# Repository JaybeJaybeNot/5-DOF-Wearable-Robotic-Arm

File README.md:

Robotic arms are a common project idea for engineers, providing the opportunity to tackle challenges such as feedback loops, PCB designing, firmware programming, and mechanical designing. The difficulty varies greatly, from using basic Microservos driven by Arduino to using industry-standard MCUs like the STM32 family to achieve impressive torque, precision, accuracy, and speed. 
Our design will lean somewhat to the right (industry-like) side of difficulty, utilizing the STM32F103C8Tx model of MCU's for performance, TMC motor drivers, the motors will be  2 NEMA 23 (QSH6018) for shoulders, and NEMA 17 (QSH6018) for elbow. Stepper motors are chosen for their high torque relative to their low costs, possibly getting away with $30 for each NEMA 23, depending on the seller. Gearboxes will be utilized for each motor to increase torque output. We'll also lean into the gritty, brutalist aesthetic of industry, partially because I had minimal CAD experience at the beginning of this project.
The "quirk" of our project is that the robotic arm will be wearable. Current design ideas include straps similar to those of a hiking backpack, but will possible change in the future due to ergonomic reasons or if I just came up with better ideas. To control the robotic arm, a GUI will be made with sliders that control each joint, and activators for motor modes (Stealthchop2, spreadcycle). 

This project was made out of a desire to learn embedded systems, firmware code, and basic mechanical design. It is also partially motivated by having Viktor from Arcane as my favorite character. 

|120R1                         |FerriteBead         |~                                                               |Inductor_SMD:L_0402_1005Metric                                                            |1  |FIELD6|
|------------------------------|--------------------|----------------------------------------------------------------|------------------------------------------------------------------------------------------|---|------|
|C1                            |680 uF              |~                                                               |Capacitor_SMD:C_1210_3225Metric                                                           |1  |      |
|C2                            |220 uF              |~                                                               |Capacitor_SMD:C_0603_1608Metric                                                           |1  |      |
|C3,C15                        |10 pF               |~                                                               |-- mixed values --                                                                        |2  |      |
|C4,C18,C19,C22,C25,C26,C27,C28|100nF               |~                                                               |-- mixed values --                                                                        |8  |      |
|C5,C24                        |2.2u, 6.3v          |~                                                               |-- mixed values --                                                                        |2  |      |
|C6,C7,C8,C9,C14               |100 nF              |~                                                               |Capacitor_SMD:C_0201_0603Metric                                                           |5  |      |
|C10                           |10 uF               |~                                                               |Capacitor_SMD:C_0201_0603Metric                                                           |1  |      |
|C11                           |10 nF               |~                                                               |Capacitor_SMD:C_0201_0603Metric                                                           |1  |      |
|C12,C13                       |1 uF                |~                                                               |Capacitor_SMD:C_0201_0603Metric                                                           |2  |      |
|C16,C17                       |22 uF               |~                                                               |Capacitor_SMD:C_0201_0603Metric                                                           |2  |      |
|C20,C29                       |100uF               |~                                                               |Capacitor_SMD:CP_Elec_5x3.9                                                               |2  |      |
|C21,C23                       |22nF                |~                                                               |Capacitor_SMD:C_0201_0603Metric                                                           |2  |      |
|D1                            |1N5824              |http://www.vishay.com/docs/88526/1n5820.pdf                     |Diode_THT:D_DO-201AD_P3.81mm_Vertical_AnodeUp                                             |1  |      |
|D2                            |LED                 |~                                                               |LED_THT:LED_D2.0mm_W4.0mm_H2.8mm_FlatTop                                                  |1  |      |
|J1,J2                         |Conn_01x04_Pin      |~                                                               |Connector:FanPinHeader_1x04_P2.54mm_Vertical                                              |2  |      |
|J3,J4,J5,J6,J7,J8,J9,J10      |Screw_Terminal_01x01|~                                                               |TerminalBlock_MetzConnect:TerminalBlock_MetzConnect_360271_1x01_Horizontal_ScrewM3.0_Boxed|8  |      |
|J11                           |Supply anode        |~                                                               |TerminalBlock_Phoenix:TerminalBlock_Phoenix_MKDS-1,5-2-5.08_1x02_P5.08mm_Horizontal       |1  |      |
|J12                           |Supply Cathode      |~                                                               |TerminalBlock_Phoenix:TerminalBlock_Phoenix_MKDS-1,5-2-5.08_1x02_P5.08mm_Horizontal       |1  |      |
|L1                            |33 uH               |~                                                               |Inductor_SMD:L_0603_1608Metric                                                            |1  |      |
|P1                            |USB_C_Plug_USB2.0   |https://www.usb.org/sites/default/files/documents/usb_type-c.zip|Connector_USB:USB_C_Plug_JAE_DX07P024AJ1                                                  |1  |      |
|R1                            |10k                 |~                                                               |Resistor_SMD:R_0603_1608Metric                                                            |1  |      |
|R2,R11,R12                    |5.1kR               |~                                                               |Resistor_SMD:R_0603_1608Metric                                                            |3  |      |
|R3,R4,R5,R6                   |1.5k                |~                                                               |Resistor_SMD:R_0603_1608Metric                                                            |4  |      |
|R7,R8,R9,R10                  |0.05 R              |~                                                               |Resistor_SMD:R_0603_1608Metric                                                            |4  |      |
|RREF1,RREF2                   |0.05R               |~                                                               |Resistor_SMD:R_0603_1608Metric                                                            |2  |      |
|SW1                           |SW_DPST_x2          |~                                                               |Button_Switch_SMD:SW_SPST_REED_CT05-XXXX-J1                                               |1  |      |
|SW2                           |SW_SPDT             |~                                                               |Button_Switch_THT:SW_Slide_SPDT_Straight_CK_OS102011MS2Q                                  |1  |      |
|U1                            |STM32F103C8Tx       |https://www.st.com/resource/en/datasheet/stm32f103c8.pdf        |Package_QFP:LQFP-48_7x7mm_P0.5mm                                                          |1  |      |
|U2                            |AMS1117-3.3         |http://www.advanced-monolithic.com/pdf/ds1117.pdf               |Package_TO_SOT_SMD:SOT-223-3_TabPin2                                                      |1  |      |
|U3,U5                         |TMC2209-LA          |TMC2209-LA                                                      |footprints:QFN28_5X5_TRI                                                                  |2  |      |
|U4                            |LM2596S-3.3         |http://www.ti.com/lit/ds/symlink/lm2596.pdf                     |Package_TO_SOT_SMD:TO-263-5_TabPin3                                                       |1  |      |
|Y1                            |16 MHz              |~                                                               |Crystal:Crystal_SMD_0603-4Pin_6.0x3.5mm                                                   |1  |      |

|Part Name                     |FIXED Modular design|FIELD3                                                          |FIELD4                                                                                    |FIELD5|FIELD6                   |FIELD7     |FIELD8   |FIELD9  |FIELD10|FIELD11 |FIELD12      |FIELD13     |
|------------------------------|--------------------|----------------------------------------------------------------|------------------------------------------------------------------------------------------|------|-------------------------|-----------|---------|--------|-------|--------|-------------|------------|
|Working BOM                   |as of July 31, 2025 at 12:54:05 AM UTC|                                                                |                                                                                          |      |                         |           |         |        |       |        |             |            |
|Exported by                   |yaoy26@okemosk12.net|                                                                |                                                                                          |      |                         |           |         |        |       |        |             |            |
|Time of Export                |12:54 AM Jul 31, 2025|                                                                |                                                                                          |      |                         |           |         |        |       |        |             |            |
|                              |                    |                                                                |                                                                                          |      |                         |           |         |        |       |        |             |            |
|Level                         |Part Number         |Part Name                                                       |External Component                                                                        |Milestone|Description              |Link       |Lifecycle|Revision|State  |Quantity|Material Name|Change Order|
|1                             |FIXED Modular design|FIXED Modular design                                            |                                                                                          |      |                         |           |         |        |Working|1       |Steel        |            |
|1.1                           |90304A311_Steel Pan Head Torx Screws|90304A311_Steel Pan Head Torx Screws                            |External                                                                                  |      |STEP AP203               |           |         |        |Working|1       |Steel        |            |
|1.2                           |FLANGE_COUPLING_W_GRUB_SCREW_ASM|flange_coupling_w_grub_screw_asm                                |External                                                                                  |      |                         |[(May not work on some browsers)](https://www.aliexpress.us/item/3256801265414698.html?gatewayAdapt=glo2usa4itemAdapt)|         |        |Working|1       |Steel        |            |
|1.2.1                         |M6X8_GRUB_SCREW     |M6X8_GRUB_SCREW                                                 |                                                                                          |      |NOT SPECIFIED            |           |         |        |Working|1       |Steel        |            |
|1.2.2                         |FLANGE_COUPLING_W_KEYWAY|FLANGE_COUPLING_W_KEYWAY                                        |                                                                                          |      |NOT SPECIFIED            |https://www.aliexpress.us/item/2255800648228548.html?spm=a2g0o.cart.0.0.35c13c00J1egBJ&mp=1&gatewayAdapt=glo2usa4itemAdapt|         |        |Working|3       |Steel        |            |
|1.3                           |23HS22-2804S-HG50   |23HS22-2804S-HG50                                               |External                                                                                  |      |STEP AP214               |https://www.omc-stepperonline.com/nema-23-stepper-motor-l-56mm-gear-ratio-50-1-high-precision-planetary-gearbox-23hs22-2804s-hg50?srsltid=AfmBOorzKo3zYEa1jqBecvxOFDW23BkeehO4uh2gfFv6ItN-vEymc9Z2|         |        |Working|4       |Steel        |            |
|1.4.1                         |M6X8_GRUB_SCREW     |M6X8_GRUB_SCREW (2)                                             |                                                                                          |      |NOT SPECIFIED            |           |         |        |Working|1       |Steel        |            |
|                              |                    |                                                                |                                                                                          |      |                         |           |         |        |       |        |             |            |
|1.5                           |90304A311_Steel Pan Head Torx Screws|90304A311_Steel Pan Head Torx Screws v1 (1)                     |                                                                                          |      |STEP AP203               |           |         |        |Working|1       |Steel        |            |
|1.6                           |Base2               |Base2                                                           |                                                                                          |      |                         |           |         |        |Working|1       |Steel        |            |
|1.7                           |Link 2              |Link 2                                                          |                                                                                          |      |                         |           |         |        |Working|1       |Steel        |            |
|1.7.1                         |ST-M2               |ST-M2 v1 (1)                                                    |                                                                                          |      |STEP AP214               |https://www.omc-stepperonline.com/nema-23-bracket-for-stepper-motor-and-geared-stepper-motor-alloy-steel-bracket-st-m2?language=en&currency=USD&srsltid=AfmBOooK8qa6g0IWq9fvevblhgD680OPMLwRSRrIZ5VgKmFI16Q3KWzENZg&gQT=1|         |        |Working|4       |Steel        |            |
|1.9                           |Base1               |Base1                                                           |                                                                                          |      |                         |           |         |        |Working|1       |Steel        |            |

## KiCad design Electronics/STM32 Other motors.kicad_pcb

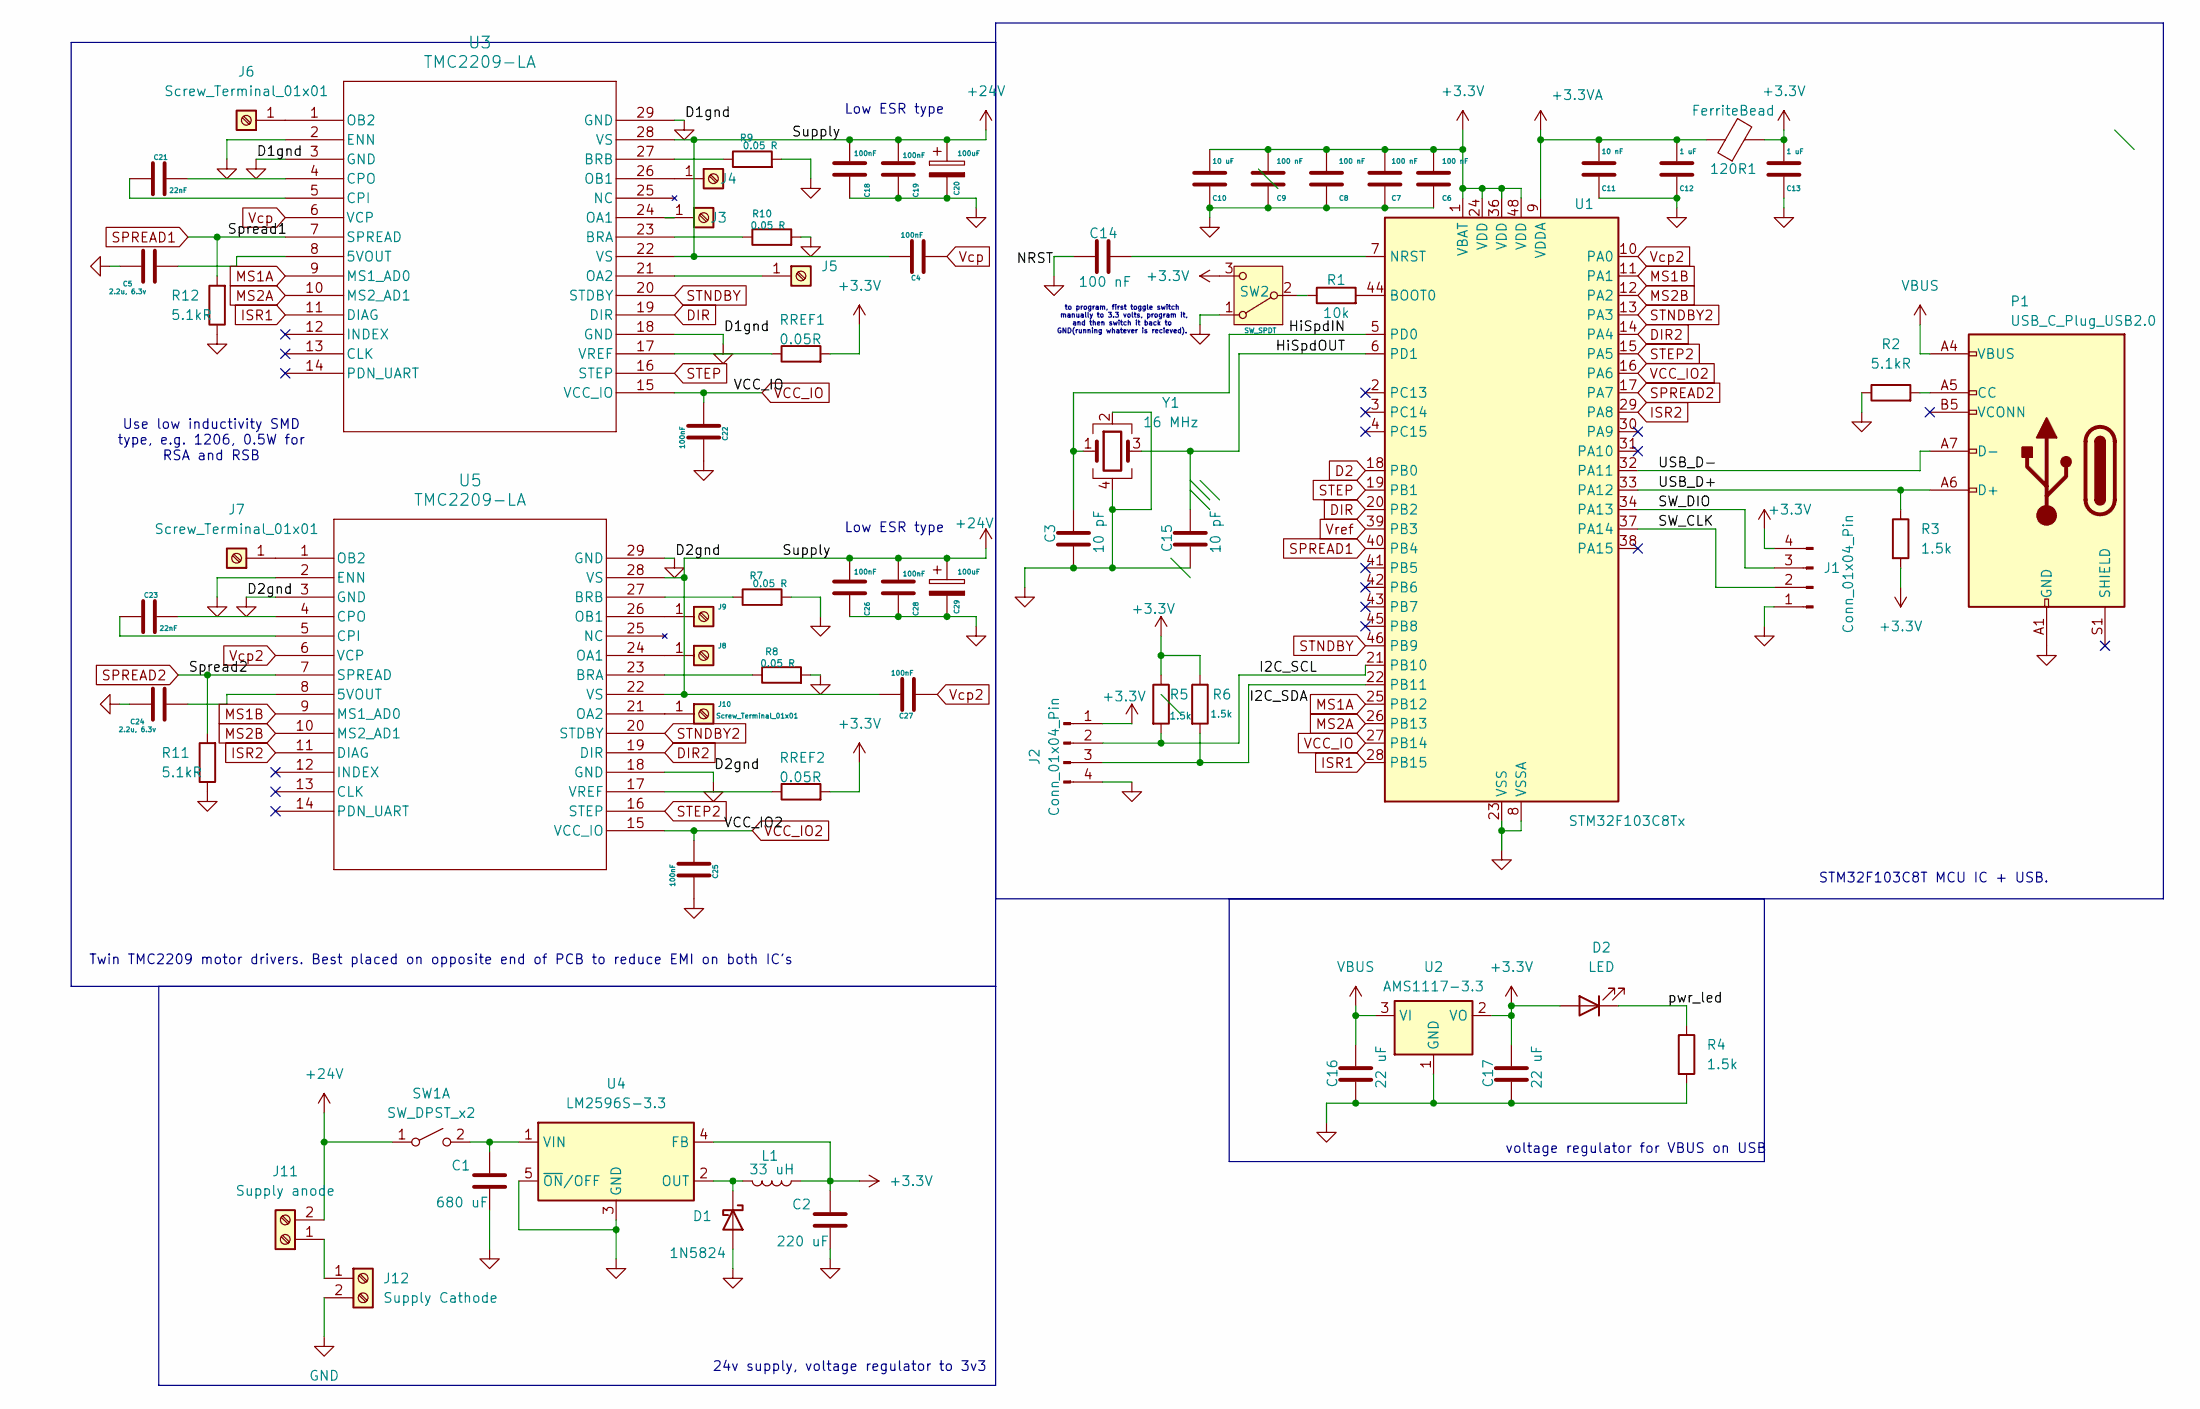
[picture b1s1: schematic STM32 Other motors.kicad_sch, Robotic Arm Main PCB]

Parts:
120R1: FerriteBead; L_0402_1005Metric
C1: 680 uF; C_1210_3225Metric
C2: 220 uF; C_0603_1608Metric
C3: 10 pF; C_0402_1005Metric
C4: 100nF; C_0402_1005Metric
C5: 2.2u, 6.3v; C_0402_1005Metric
C6, C7, C8, C9, C14: 100 nF; C_0201_0603Metric
C10: 10 uF; C_0201_0603Metric
C11: 10 nF; C_0201_0603Metric
C12, C13: 1 uF; C_0201_0603Metric
C15: 10 pF; C_0201_0603Metric
C16, C17: 22 uF; C_0201_0603Metric
C18, C19, C22, C25, C26, C27, C28: 100nF; C_0201_0603Metric
C20, C29: 100uF; CP_Elec_5x3.9
C21, C23: 22nF; C_0201_0603Metric
C24: 2.2u, 6.3v; C_0201_0603Metric
D1: 1N5824; D_DO-201AD_P3.81mm_Vertical_AnodeUp
D2: LED; LED_D2.0mm_W4.0mm_H2.8mm_FlatTop
J1, J2: Conn_01x04_Pin; FanPinHeader_1x04_P2.54mm_Vertical
J3, J4, J5, J6, J7, J8, J9, J10: Screw_Terminal_01x01; TerminalBlock_MetzConnect_360271_1x01_Horizontal_ScrewM3.0_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
J11: Supply anode; TerminalBlock_Phoenix_MKDS-1,5-2-5.08_1x02_P5.08mm_Horizont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
J12: Supply Cathode; TerminalBlock_Phoenix_MKDS-1,5-2-5.08_1x02_P5.08mm_Horizont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
L1: 33 uH; L_0603_1608Metric
P1: USB_C_Plug_USB2.0; USB_C_Plug_JAE_DX07P024AJ1
R1: 10k; R_0603_1608Metric
R2, R11, R12: 5.1kR; R_0603_1608Metric
R3, R4, R5, R6: 1.5k; R_0603_1608Metric
R7, R8, R9, R10: 0.05 R; R_0603_1608Metric
RREF1, RREF2: 0.05R; R_0603_1608Metric
SW1: SW_DPST_x2; SW_SPST_REED_CT05-XXXX-J1
SW2: SW_SPDT; SW_Slide_SPDT_Straight_CK_OS102011MS2Q
U1: STM32F103C8Tx; LQFP-48_7x7mm_P0.5mm
U2: AMS1117-3.3; SOT-223-3_TabPin2
U3, U5: TMC2209-LA; QFN28_5X5_TRI
U4: LM2596S-3.3; TO-263-5_TabPin3
Y1: 16 MHz; Crystal_SMD_0603-4Pin_6.0x3.5mm

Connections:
+3.3V: 120R1.2, C2.2, C6.2, C7.2, C8.2, C9.2, C10.2, C13.2, C17.1, D2.2 (A), J1.4, J2.1, L1.1, R3.2, R5.1, R6.1, RREF1.2, RREF2.2, SW2.3 (C), U1.1 (VBAT), U1.24 (VDD), U1.36 (VDD), U1.48 (VDD), U2.2 (VO), U4.4 (FB)
+3.3VA: 120R1.1, C11.2, C12.2, U1.9 (VDDA)
+24V: C4.2, C18.2, C19.2, C20.1, C26.2, C27.2, C28.2, C29.1, J11.2, SW1.1 (A), U3.22 (VS), U3.28 (VS), U5.22 (VS), U5.28 (VS)
/HiSpdIN: C3.1, U1.5 (PD0), Y1.1
/HiSpdOUT: C15.1, U1.6 (PD1), Y1.3
/I2C_SCL: J2.2, R5.2, U1.21 (PB10)
/I2C_SDA: J2.3, R6.2, U1.22 (PB11)
/SW_CLK: J1.2, U1.37 (PA14)
/SW_DIO: J1.3, U1.34 (PA13)
/USB_D+: P1.A6 (D+), R3.1, U1.33 (PA12)
/USB_D-: P1.A7 (D-), U1.32 (PA11)
/pwr_led: D2.1 (K), R4.1
D2: U1.18 (PB0)
DIR: U1.20 (PB2), U3.19 (DIR)
DIR2: U1.14 (PA4), U5.19 (DIR)
GND: C1.1, C2.1, C3.2, C5.1, C6.1, C7.1, C8.1, C9.1, C10.1, C11.1, C12.1, C13.1, C14.2, C15.2, C16.2, C17.2, C18.1, C19.1, C20.2, C22.2, C24.1, C25.2, C26.1, C28.1, C29.2, D1.2 (A), J1.1, J2.4, J12.2, P1.A1 (GND), P1.A12 (GND), P1.B1 (GND), P1.B12 (GND), R2.1, R4.2, R7.2, R8.2, R9.2, R10.2, R11.1, R12.1, SW2.1 (A), U1.8 (VSSA), U1.23 (VSS), U1.35 (VSS), U1.47 (VSS), U2.1 (GND), U3.2 (ENN), U3.3 (GND), U3.18 (GND), U3.29 (GND), U4.3 (GND), U4.5 (~ON/OFF), U5.2 (ENN), U5.3 (GND), U5.18 (GND), U5.29 (GND), Y1.2, Y1.4
ISR1: U1.28 (PB15), U3.11 (DIAG)
ISR2: U1.29 (PA8), U5.11 (DIAG)
MS1A: U1.25 (PB12), U3.9 (MS1_AD0)
MS1B: U1.11 (PA1), U5.9 (MS1_AD0)
MS2A: U1.26 (PB13), U3.10 (MS2_AD1)
MS2B: U1.12 (PA2), U5.10 (MS2_AD1)
unnamed: D1.1 (K), L1.2, U4.2 (OUT)
unnamed: J3.1, U3.24 (OA1)
unnamed: J4.1, U3.26 (OB1)
unnamed: J5.1, U3.21 (OA2)
unnamed: J6.1, U3.1 (OB2)
unnamed: J7.1, U5.1 (OB2)
unnamed: J8.1, U5.24 (OA1)
unnamed: J9.1, U5.26 (OB1)
unnamed: J10.1, U5.21 (OA2)
unnamed: J11.1, J12.1
unnamed: P1.A5 (CC), R2.2
unnamed: C1.2, SW1.2 (B), U4.1 (VIN)
unnamed: R1.1, SW2.2 (B)
unnamed: R1.2, U1.44 (BOOT0)
unnamed: C14.1, U1.7 (NRST)
unnamed: C5.2, U3.8 (5VOUT)
unnamed: R10.1, U3.23 (BRA)
unnamed: R9.1, U3.27 (BRB)
unnamed: C21.1, U3.5 (CPI)
unnamed: C21.2, U3.4 (CPO)
unnamed: RREF1.1, U3.17 (VREF)
unnamed: C24.2, U5.8 (5VOUT)
unnamed: R8.1, U5.23 (BRA)
unnamed: R7.1, U5.27 (BRB)
unnamed: C23.1, U5.5 (CPI)
unnamed: C23.2, U5.4 (CPO)
unnamed: RREF2.1, U5.17 (VREF)
SPREAD1: R12.2, U1.40 (PB4), U3.7 (SPREAD)
SPREAD2: R11.2, U1.17 (PA7), U5.7 (SPREAD)
STEP: U1.19 (PB1), U3.16 (STEP)
STEP2: U1.15 (PA5), U5.16 (STEP)
STNDBY: U1.46 (PB9), U3.20 (STDBY)
STNDBY2: U1.13 (PA3), U5.20 (STDBY)
VBUS: C16.1, P1.A4 (VBUS), P1.A9 (VBUS), P1.B4 (VBUS), P1.B9 (VBUS), U2.3 (VI)
VCC_IO: C22.1, U1.27 (PB14), U3.15 (VCC_IO)
VCC_IO2: C25.1, U1.16 (PA6), U5.15 (VCC_IO)
Vcp: C4.1, U3.6 (VCP)
Vcp2: C27.1, U1.10 (PA0), U5.6 (VCP)
Vref: U1.39 (PB3)

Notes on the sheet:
Twin TMC2209 motor drivers. Best placed on opposite end of PCB to reduce EMI on both IC's
24v supply, voltage regulator to 3v3
to program, first toggle switch manually to 3.3 volts, program it, and then switch it back to GND(running whatever is recieved).
Low ESR type
STM32F103C8T MCU IC + USB.
Use low inductivity SMD type, e.g. 1206, 0.5W for RSA and RSB
voltage regulator for VBUS on USB

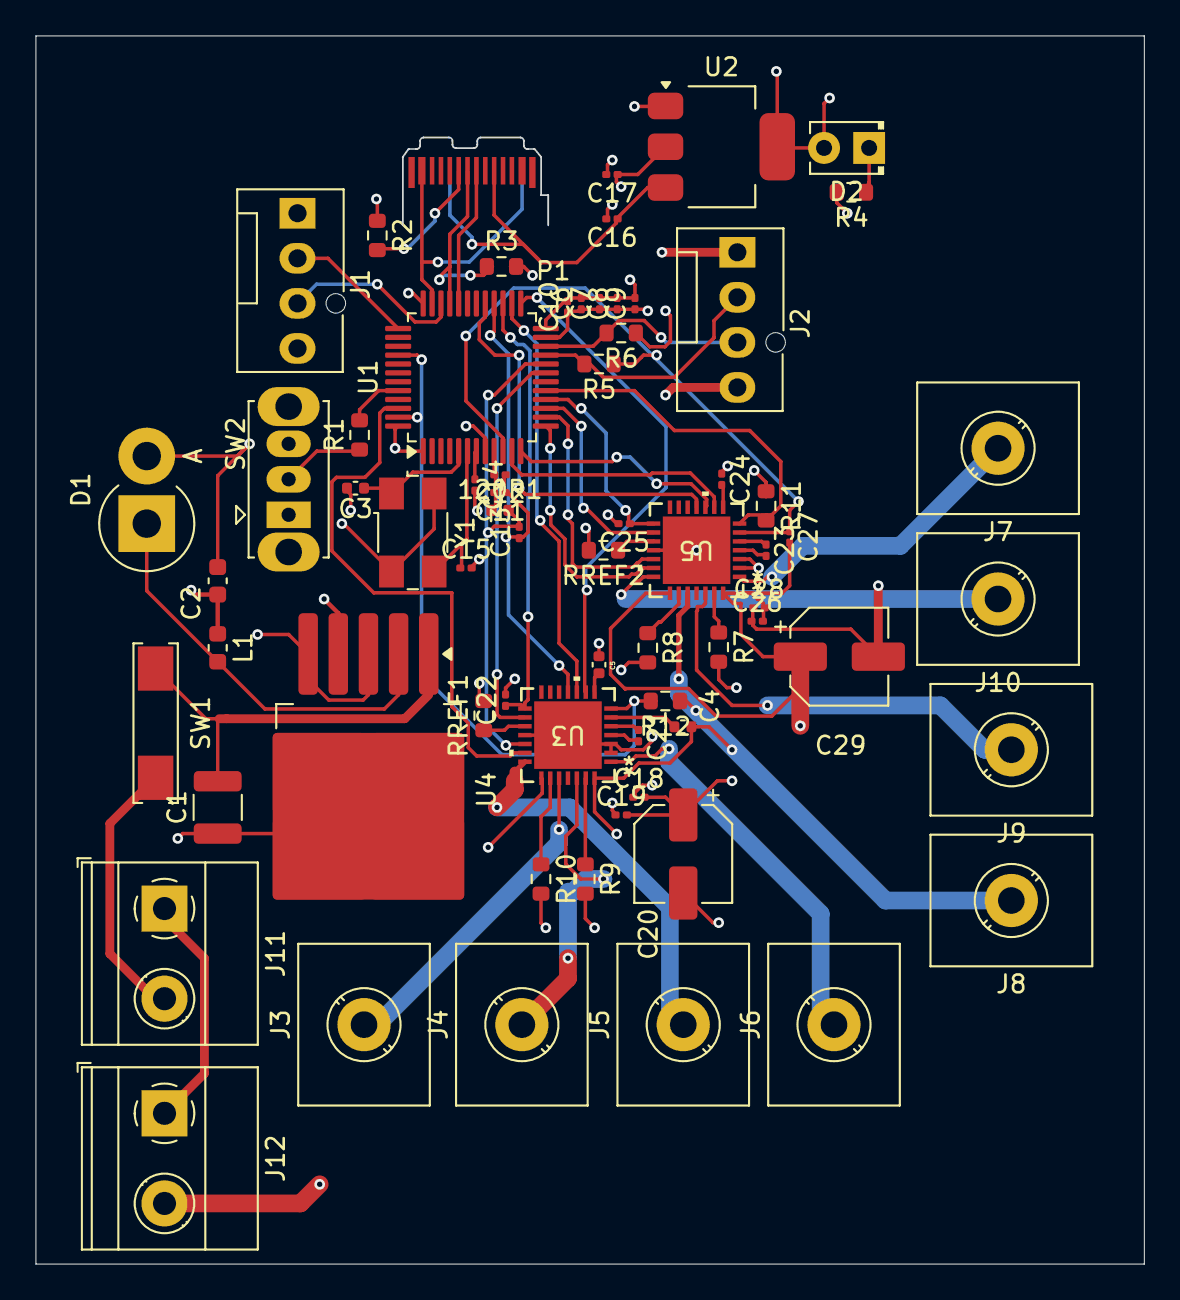
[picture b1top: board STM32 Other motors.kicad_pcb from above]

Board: 4 copper layers, 62.5 x 69.2 mm, 68 parts (0 on the bottom side), 59 nets.

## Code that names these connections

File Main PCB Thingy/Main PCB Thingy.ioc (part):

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Mcu.Name=STM32F103C(8-B)Tx
Mcu.Package=LQFP48
Mcu.UserName=STM32F103C8Tx
PA0-WKUP.GPIOParameters=GPIO_Label
PA0-WKUP.GPIO_Label=Vcp2
PA0-WKUP.Signal=GPIO_Output
PA1.GPIOParameters=GPIO_Label
PA1.GPIO_Label=MS1B
PA1.Signal=GPIO_Output
PA11.GPIOParameters=GPIO_Label
PA11.GPIO_Label=USB_D+
PA11.Mode=Device
PA11.Signal=USB_DM
PA12.GPIOParameters=GPIO_Label
PA12.GPIO_Label=USB_D-
PA12.Mode=Device
PA12.Signal=USB_DP
PA13.Signal=SYS_JTMS-SWDIO
PA14.Signal=SYS_JTCK-SWCLK
PA2.GPIOParameters=GPIO_Label
PA2.GPIO_Label=MS2B
PA2.Signal=GPIO_Output
PA3.GPIOParameters=GPIO_Label
PA3.GPIO_Label=STNDBY2
PA3.Signal=GPIO_Output
PA4.GPIOParameters=GPIO_Label
PA4.GPIO_Label=DIR2
PA4.Signal=GPIO_Output
PA5.GPIOParameters=GPIO_Label
PA5.GPIO_Label=STEP2
PA5.Signal=GPIO_Output
PA6.GPIOParameters=GPIO_Label
PA6.GPIO_Label=VCC_IO2
PA6.Signal=GPIO_Output
PA7.GPIOParameters=GPIO_Label
PA7.GPIO_Label=SPREAD2
PA7.Signal=GPIO_Output
PA8.GPIOParameters=GPIO_Label
PA8.GPIO_Label=ISR2
PA8.Signal=GPIO_Output
PB0.GPIOParameters=GPIO_Label
PB0.GPIO_Label=D2
PB0.Signal=GPIO_Output
PB1.GPIOParameters=GPIO_Label
PB1.GPIO_Label=STEP
PB1.Signal=GPIO_Output
PB10.Signal=I2C2_SCL
PB11.Signal=I2C2_SDA
PB12.GPIOParameters=GPIO_Label
PB12.GPIO_Label=MS1A
PB12.Signal=GPIO_Output
PB13.GPIOParameters=GPIO_Label
PB13.GPIO_Label=MS2A
PB13.Signal=GPIO_Output
PB14.GPIOParameters=GPIO_Label
PB14.GPIO_Label=VCC_IO
PB14.Signal=GPIO_Output
PB15.GPIOParameters=GPIO_Label
PB15.GPIO_Label=ISR1
PB15.Signal=GPIO_Output
PB2.GPIOParameters=GPIO_Label
PB2.GPIO_Label=DIR
PB2.Signal=GPIO_Output
PB3.GPIOParameters=GPIO_Label
PB3.GPIO_Label=Vref
PB3.Signal=GPIO_Output
PB4.GPIOParameters=GPIO_Label
PB4.GPIO_Label=SPREAD1
PB4.Signal=GPIO_Output
PB9.GPIOParameters=GPIO_Label
PB9.GPIO_Label=STNDBY
PB9.Signal=GPIO_Output
PC14-OSC32_IN.Mode=LSE-External-Oscillator
PC14-OSC32_IN.Signal=RCC_OSC32_IN
PC15-OSC32_OUT.Mode=LSE-External-Oscillator
PC15-OSC32_OUT.Signal=RCC_OSC32_OUT
PD0-OSC_IN.Mode=HSE-External-Oscillator
PD0-OSC_IN.Signal=RCC_OSC_IN
PD1-OSC_OUT.Mode=HSE-External-Oscillator
PD1-OSC_OUT.Signal=RCC_OSC_OUT
RCC.HSE_VALUE=16000000
RCC.SYSCLKFreq_VALUE=48000000
RCC.SYSCLKSource=RCC_SYSCLKSOURCE_PLLCLK
board=custom

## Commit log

2025-07-06 Update JOURNAL.md
    Eh, i don't want to pad the journal
2025-07-06 Add files via upload
    the STM32 configuration files on STM32CubeIDE
